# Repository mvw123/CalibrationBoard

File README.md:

CalibrationBoard
================

Reference board for calibration of Voltage, current, resistance Capacitance and Inductance
The design is created in Eagle CAD v 6.5.0 (free version) and uses the standard PCB board size.

CAD B - [WIP]
====================================
Work in progress

CAD A - [WIP]
====================================

The board has been manufactured at PCB fabricator ITead
Some issues have been noted with the PCB. See issues list in github. 

Basic tests indicate the board works, but needs a CAD B to correct some PCB issues. 

Specification: 
==============
Voltage reference -> 2.5V and 5.0V < 10mA load
Current Reference -> Configurable up to 10A max
Resistance references -> Various tight tolerance resistors <=1 ohm = 1%, >1 ohm = 0.1%
Capacitors -> TBD
Inductors -> TBD

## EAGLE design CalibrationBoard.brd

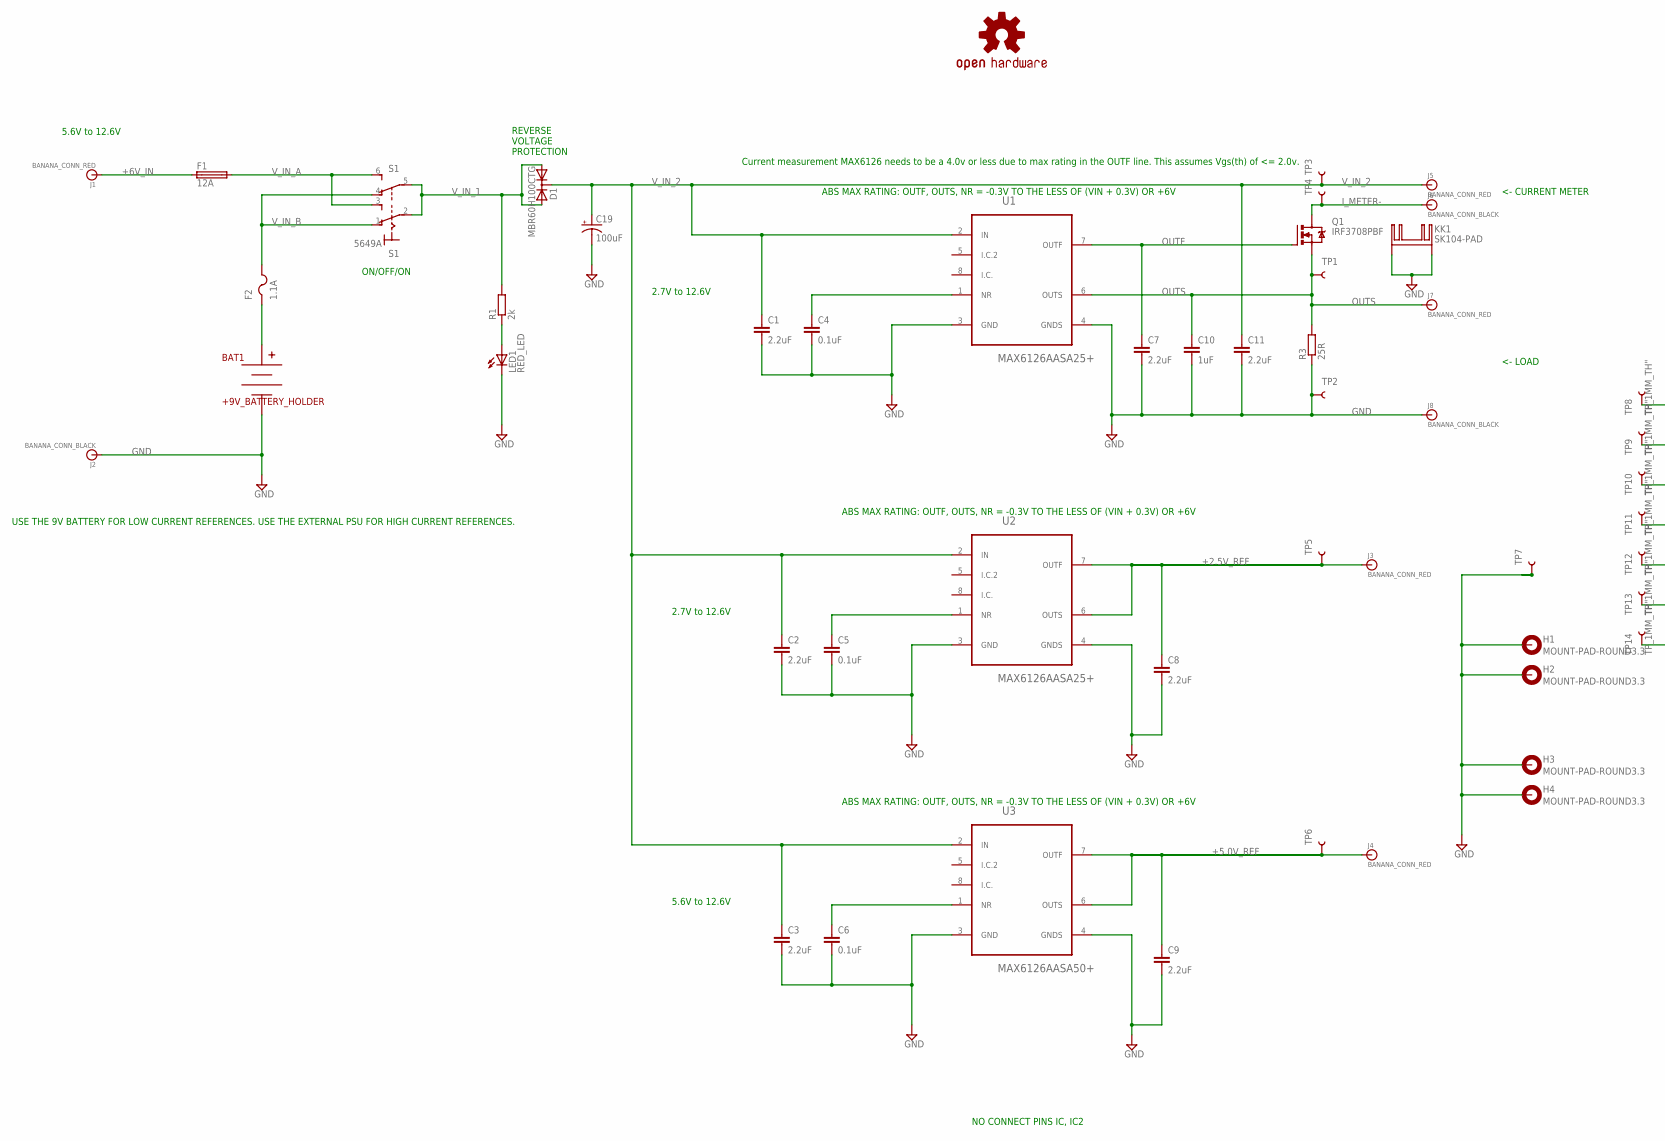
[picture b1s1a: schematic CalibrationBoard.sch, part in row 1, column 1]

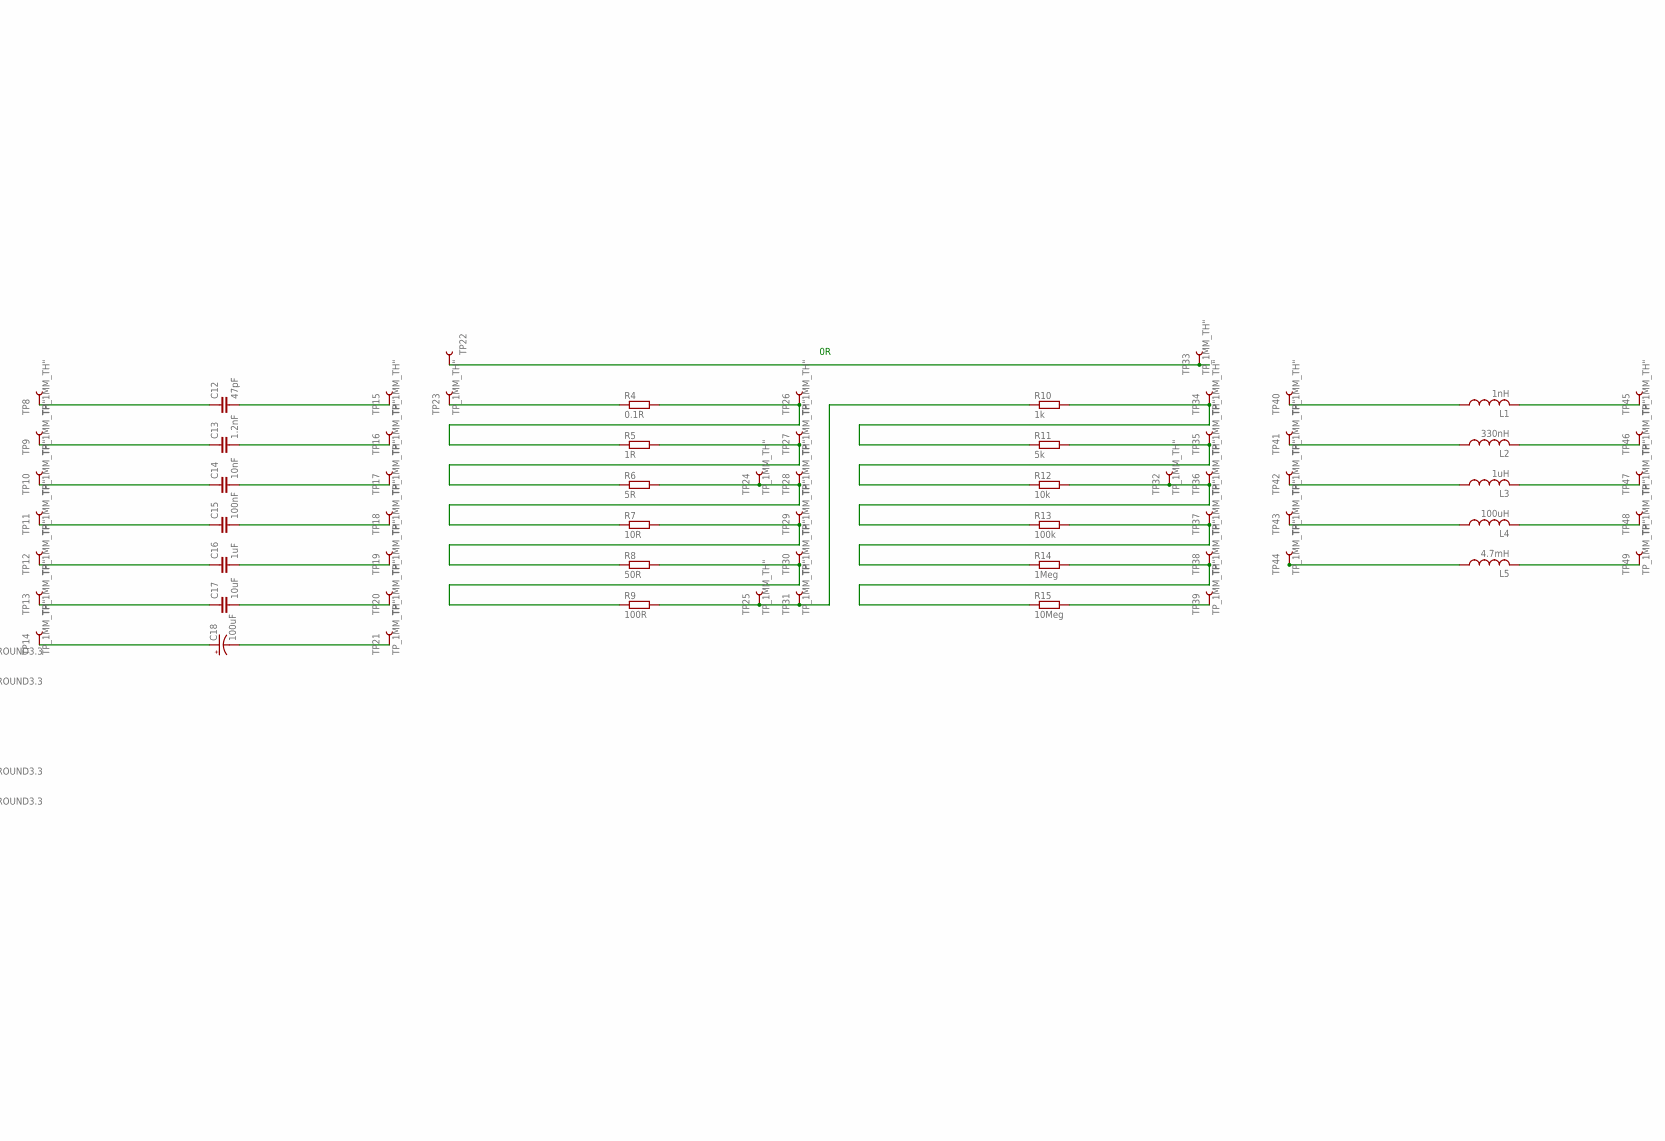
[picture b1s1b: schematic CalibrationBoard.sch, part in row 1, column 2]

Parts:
BAT1: +9V_BATTERY_HOLDER; BC9VPC
C1, C2, C3, C7, C8, C9, C11: 2.2uF; C0805
C4, C5, C6: 0.1uF; C0805
C10, C16: 1uF; C0805
C12: 47pF; C0805; MPN 08052U470FAT2A
C13: 1.2nF; C0805; MPN VJ0805A122FXBMT
C14: 10nF; C0805
C15: 100nF; C0805; MPN 08055C104JAT2A
C17: 10uF; C0805
C18, C19: 100uF; E5-10,5
D1: MBR60H100CTG; TO220ABS; MPN MBR60H100CTG
F1: 12A; RGEF1200
F2: 1.1A; 1812; MPN MINISMDC110F/24-2
H1, H2, H3, H4: MOUNT-PAD-ROUND3.3; 3,3-PAD
J1, J3, J4, J5, J7: BANANA_CONN_RED; BANANA_CONN; MPN 972354101
J2, J6, J8: BANANA_CONN_BLACK; BANANA_CONN; MPN 972354101
KK1: SK104-PAD; MPN SK 129 38,1 STS
L1: 1nH; L1812
L2: 330nH; L2825P; MPN CW252016-R33G
L3: 1uH; L1812; MPN 1812PS-102JLC
L4: 100uH; L1812; MPN 1812PS-104JLB
L5: 4.7mH; 6000-XXXX-RC; MPN 7447721047
LED1: RED_LED; P-LCC-2; MPN 597-3121-207F
LOGO1: OSHW-LOGOL; OSHW-LOGO-L
Q1: IRF3708PBF; TO220BV; MPN IRF3708PBF
R1: 2k; R0805
R3: 25R; R0805
R4: 0.1R; R0805; MPN ERJ6RSFR10V
R5: 1R; R0805; MPN CR0805-FX-1R00ELF
R6: 5R; R0805
R7: 10R; R0805; MPN CRT0805-BY-10R0ELF
R8: 50R; R0805
R9: 100R; R0805; MPN RR1220P-101-B-T5
R10: 1k; R0805; MPN ERA6AEB102V
R11: 5k; R0805
R12: 10k; R0805; MPN RR1220P-103-B-T5
R13: 100k; R0805; MPN RR1220P-104-B-T5
R14: 1Meg; R0805; MPN RR1220P-105-B-T5
R15: 10Meg; R0805
S1: 5649A; 320-938; MPN 5649A
TP1, TP2, TP3, TP4, TP5, TP6, TP7, TP8, TP9, TP10, TP11, TP12, TP13, TP14, TP15, TP16, TP17, TP18, TP19, TP20, TP21, TP22, TP23, TP24, TP25, TP26, TP27, TP28, TP29, TP30, TP31, TP32, TP33, TP34, TP35, TP36, TP37, TP38, TP39, TP40, TP41, TP42, TP43, TP44, TP45, TP46, TP47, TP48, TP49: TP_1MM_TH"; TP_1MM_TH; MPN TEST-3
U1, U2: MAX6126AASA25+; SOIC127P600X175-8N; MPN MAX6126AASA25+
U3: MAX6126AASA50+; SOIC127P600X175-8N

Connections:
+2.5V_REF: C8.1, J3.P$1, TP5.P$1, U2.6 (OUTS), U2.7 (OUTF)
+5.0V_REF: C9.1, J4.P$1, TP6.P$1, U3.6 (OUTS), U3.7 (OUTF)
+6V_IN: F1.1, J1.P$1
GND: BAT1.V-, C1.2, C2.2, C3.2, C4.2, C5.2, C6.2, C7.2, C8.2, C9.2, C10.2, C11.2, C19.-, H1.B3,3, H2.B3,3, H3.B3,3, H4.B3,3, J2.P$1, J8.P$1, KK1.K1, KK1.K2, LED1.C, R3.1, TP2.P$1, TP7.P$1, U1.3 (GND), U1.4 (GNDS), U2.3 (GND), U2.4 (GNDS), U3.3 (GND), U3.4 (GNDS)
I_METER-: J6.P$1, Q1.D, TP4.P$1
unnamed: C12.1, TP8.P$1
unnamed: L1.2, TP45.P$1
unnamed: R4.1, TP23.P$1
unnamed: C6.1, U3.1 (NR)
unnamed: L2.2, TP46.P$1
unnamed: R8.2, R9.1, TP30.P$1
unnamed: BAT1.V+, F2.1
unnamed: R4.2, R5.1, TP26.P$1
unnamed: C17.2, TP20.P$1
unnamed: R9.2, R10.1, TP25.P$1, TP31.P$1
unnamed: R10.2, R11.1, TP34.P$1
unnamed: L3.2, TP47.P$1
unnamed: C5.1, U2.1 (NR)
unnamed: R11.2, R12.1, TP35.P$1
unnamed: R13.2, R14.1, TP37.P$1
unnamed: R6.2, R7.1, TP24.P$1, TP28.P$1
unnamed: L4.2, TP48.P$1
unnamed: L5.2, TP49.P$1
unnamed: R14.2, R15.1, TP38.P$1
unnamed: TP22.P$1, TP33.P$1
unnamed: L1.1, TP40.P$1
unnamed: R15.2, TP39.P$1
unnamed: C18.+, TP14.P$1
unnamed: C18.-, TP21.P$1
unnamed: C4.1, U1.1 (NR)
unnamed: R7.2, R8.1, TP29.P$1
unnamed: LED1.A, R1.1
unnamed: R5.2, R6.1, TP27.P$1
unnamed: R12.2, R13.1, TP32.P$1, TP36.P$1
unnamed: C12.2, TP15.P$1
unnamed: C13.2, TP16.P$1
unnamed: C14.2, TP17.P$1
unnamed: C15.2, TP18.P$1
unnamed: C16.2, TP19.P$1
unnamed: C13.1, TP9.P$1
unnamed: C14.1, TP10.P$1
unnamed: C15.1, TP11.P$1
unnamed: C16.1, TP12.P$1
unnamed: C17.1, TP13.P$1
unnamed: L5.1, TP44.P$1
unnamed: L4.1, TP43.P$1
unnamed: L3.1, TP42.P$1
unnamed: L2.1, TP41.P$1
OUTF: C7.1, Q1.G, U1.7 (OUTF)
OUTS: C10.1, J7.P$1, Q1.S, R3.2, TP1.P$1, U1.6 (OUTS)
V_IN_1: D1.A1, D1.A2, R1.2, S1.2, S1.5
V_IN_2: C1.1, C2.1, C3.1, C11.1, C19.+, D1.C, J5.P$1, TP3.P$1, U1.2 (IN), U2.2 (IN), U3.2 (IN)
V_IN_A: F1.2, S1.3 (S), S1.6 (S)
V_IN_B: F2.2, S1.1 (O), S1.4 (O)

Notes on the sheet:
Current measurement MAX6126 needs to be a 4.0v or less due to max rating in the OUTF line. This assumes Vgs(th) of <= 2.0v.
2.7V to 12.6V
ABS MAX RATING: OUTF, OUTS, NR = -0.3V TO THE LESS OF (VIN + 0.3V) OR +6V
5.6V to 12.6V
<- LOAD
<- CURRENT METER
USE THE 9V BATTERY FOR LOW CURRENT REFERENCES. USE THE EXTERNAL PSU FOR HIGH CURRENT REFERENCES.
NO CONNECT PINS IC, IC2
REVERSE VOLTAGE PROTECTION
ON/OFF/ON

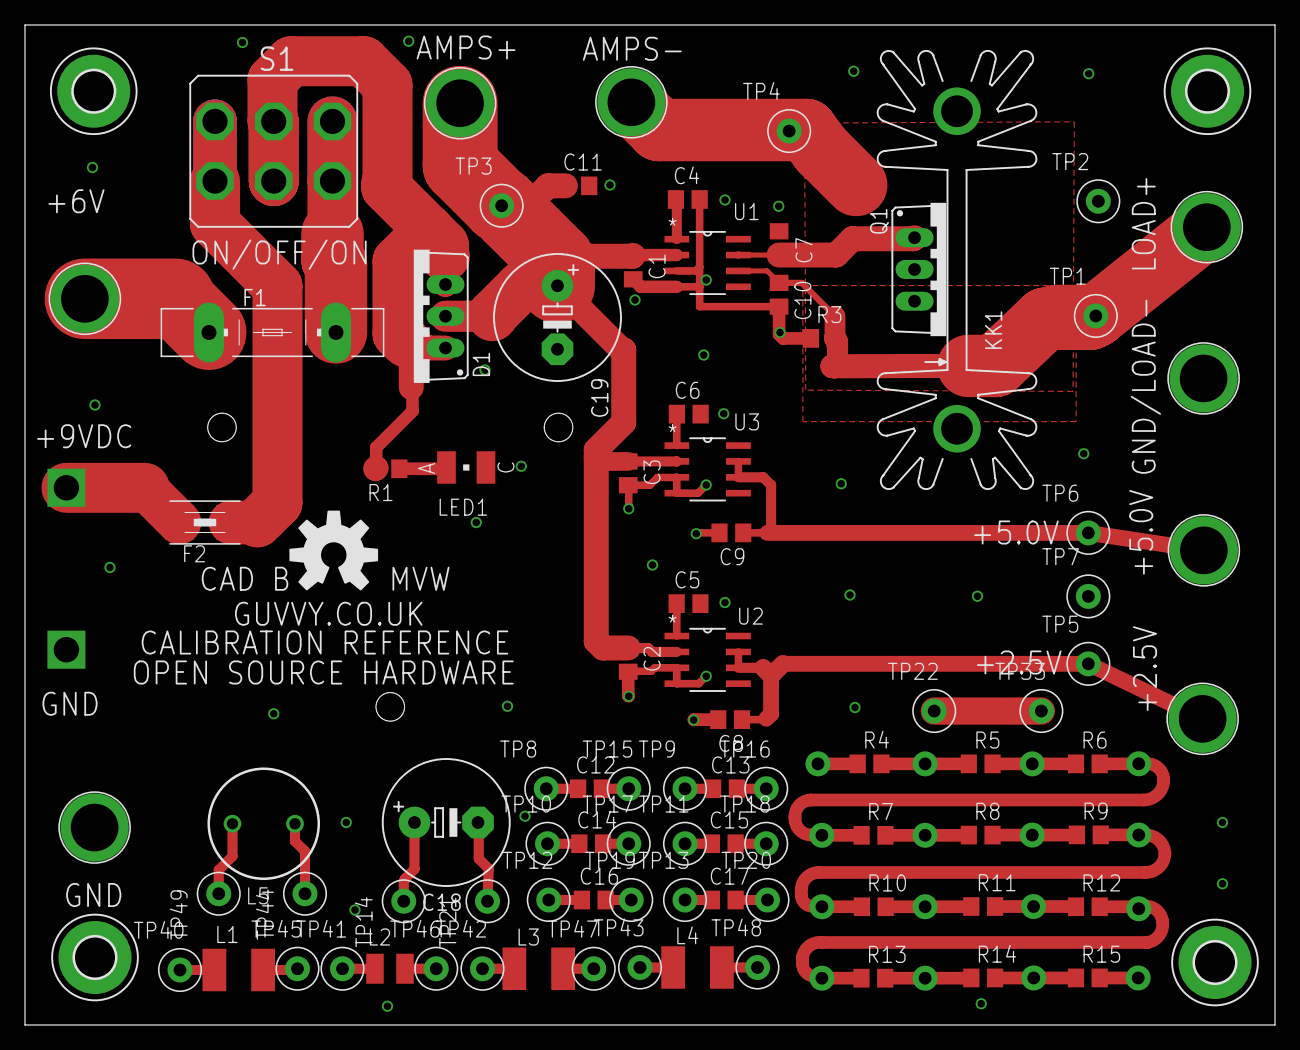
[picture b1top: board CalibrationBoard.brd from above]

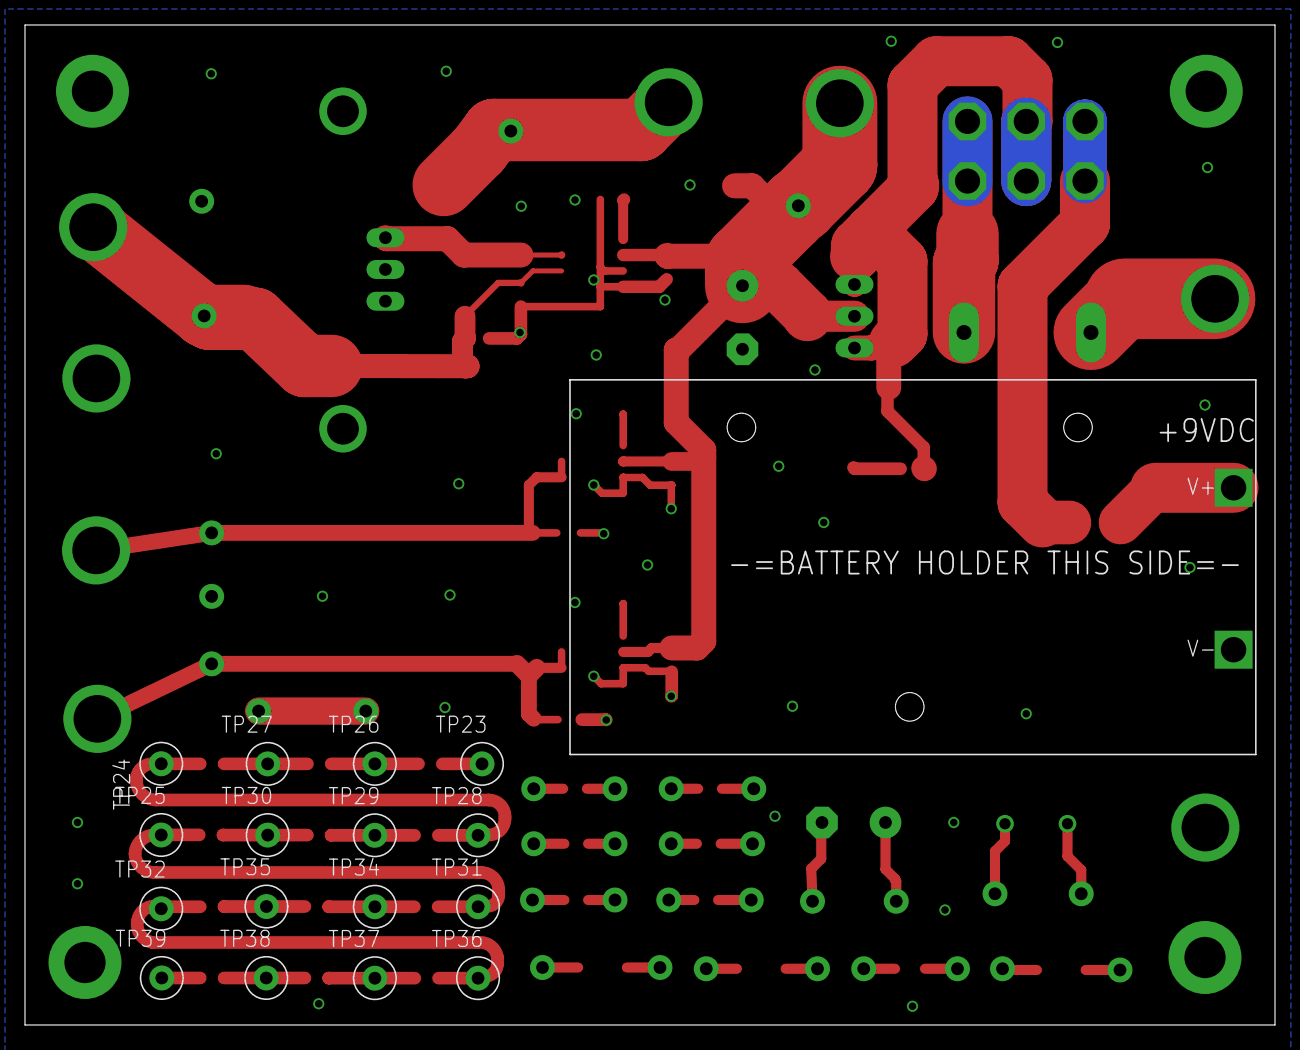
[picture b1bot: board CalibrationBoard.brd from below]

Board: 2 copper layers, 100.0 x 80.0 mm, 111 parts (17 on the bottom side), 54 nets.

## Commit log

2014-11-24 First Commit of CAD A - Still WIP
    First Commit of CAD A - Still WIP
    Needs ICs changing to MX6126 to allow only 9V operation and various
    other updates.
2014-12-10 Updates to CAD layout
    moved TH to top side, SMDs are on bottom side
2014-12-21 Added capacitors and inductors
    Added capacitors and inductors and corrected some ERC errors
2014-12-27 Updates before PCB release to Fabrication
    Updates before PCB release to Fabrication.
    Component part numbers for purchase still need specifying.
2014-12-27 Updated read description to mention eagle cad
    Updated read description to mention eagle cad
2014-12-27 minor change to project file
    minor change to project file
2014-12-31 Various minor changes with minor CAD impacts
    Connected some minor air nets (no CAD issues)
    Changed NR caps from 1uF to 0.1uF as per DS.
    Moved a decoupling cap to allow ground flood to IC.
    Standardised the plane to track separation.
2015-01-11 updates after initial testing of board.
    updates after initial testing of board.
2015-01-11 minor update after testing.
2015-02-15 latest commits
2016-01-15 latest updates
2016-01-15 no updates
    no updates
2016-01-26 no physical changes
    no physical changes
2017-09-25 project file updates

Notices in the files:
parts and their libraries:
SparkFun-Connectors: Licensing: Creative Commons ShareAlike 4.0 International - https://creativecommons.org/licenses/by-sa/4.0
